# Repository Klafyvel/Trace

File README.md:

Trace
=====

Trace est un projet ayant pour but de créer une traçeuse à commande numérique. Le projet comprend :
- Un utilitaire python pour formater le GCode et le stramer via une liason série à la machine
- Le code (arduino) de la machine qui interprète le GCode et contrôle la machine
- Le plan de la machine (électronique + mécanique)

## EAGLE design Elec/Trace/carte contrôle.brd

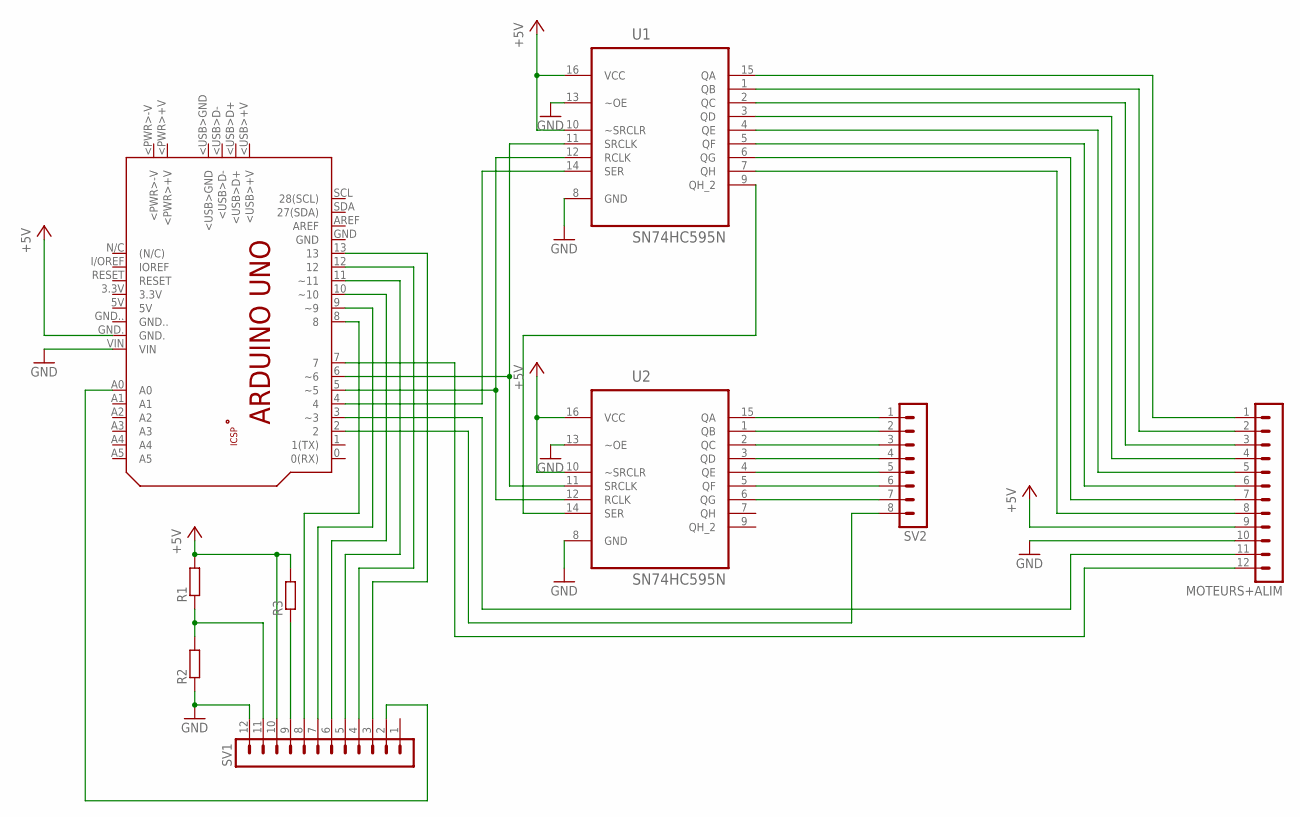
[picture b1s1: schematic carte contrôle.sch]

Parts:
MOTEURS+ALIM: MA12-1
PCB1: ARDUINO_UNO
R1, R2, R3: R-EU_0207/10; 0207/10
SV1: MA12-1
SV2: MA08-1
U1, U2: SN74HC595N; DIP254P762X508-16

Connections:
+5V: MOTEURS+ALIM.9, PCB1.GND., R1.2, R3.2, SV1.10, U1.10 (~SRCLR), U1.16 (VCC), U2.10 (~SRCLR), U2.16 (VCC)
GND: MOTEURS+ALIM.10, PCB1.VIN, R2.1, SV1.12, U1.8 (GND), U1.13 (~OE), U2.8 (GND), U2.13 (~OE)
unnamed: U1.9 (QH_2), U2.14 (SER)
unnamed: MOTEURS+ALIM.1, U1.15 (QA)
unnamed: MOTEURS+ALIM.2, U1.1 (QB)
unnamed: MOTEURS+ALIM.3, U1.2 (QC)
unnamed: MOTEURS+ALIM.4, U1.3 (QD)
unnamed: MOTEURS+ALIM.5, U1.4 (QE)
unnamed: MOTEURS+ALIM.6, U1.5 (QF)
unnamed: MOTEURS+ALIM.7, U1.6 (QG)
unnamed: MOTEURS+ALIM.8, U1.7 (QH)
unnamed: PCB1.5 (~5), U1.12 (RCLK), U2.12 (RCLK)
unnamed: PCB1.6 (~6), U1.11 (SRCLK), U2.11 (SRCLK)
unnamed: PCB1.4, U1.14 (SER)
unnamed: SV2.1, U2.15 (QA)
unnamed: SV2.2, U2.1 (QB)
unnamed: SV2.3, U2.2 (QC)
unnamed: SV2.4, U2.3 (QD)
unnamed: SV2.5, U2.4 (QE)
unnamed: SV2.6, U2.5 (QF)
unnamed: SV2.7, U2.6 (QG)
unnamed: MOTEURS+ALIM.11, PCB1.3 (~3)
unnamed: PCB1.2, SV2.8
unnamed: PCB1.8, SV1.8
unnamed: R1.1, R2.2, SV1.11
unnamed: PCB1.9 (~9), SV1.7
unnamed: PCB1.10 (~10), SV1.6
unnamed: PCB1.11 (~11), SV1.5
unnamed: PCB1.12, SV1.4
unnamed: PCB1.13, SV1.3
unnamed: R3.1, SV1.9
unnamed: PCB1.A0, SV1.2
unnamed: MOTEURS+ALIM.12, PCB1.7

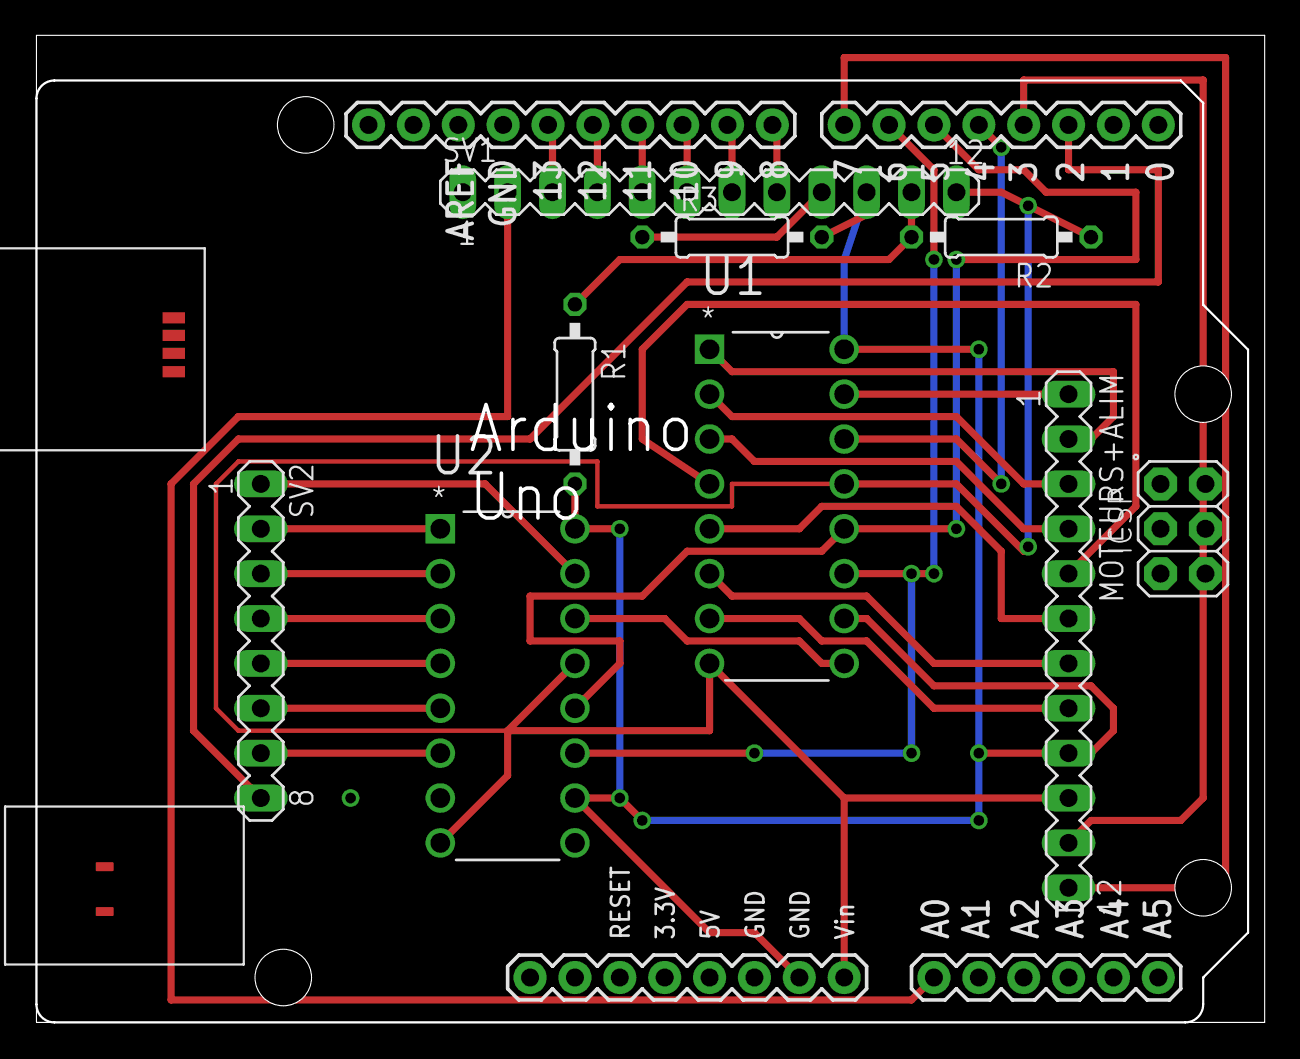
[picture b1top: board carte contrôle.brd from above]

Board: 2 copper layers, 69.5 x 55.8 mm, 9 parts (0 on the bottom side), 33 nets.

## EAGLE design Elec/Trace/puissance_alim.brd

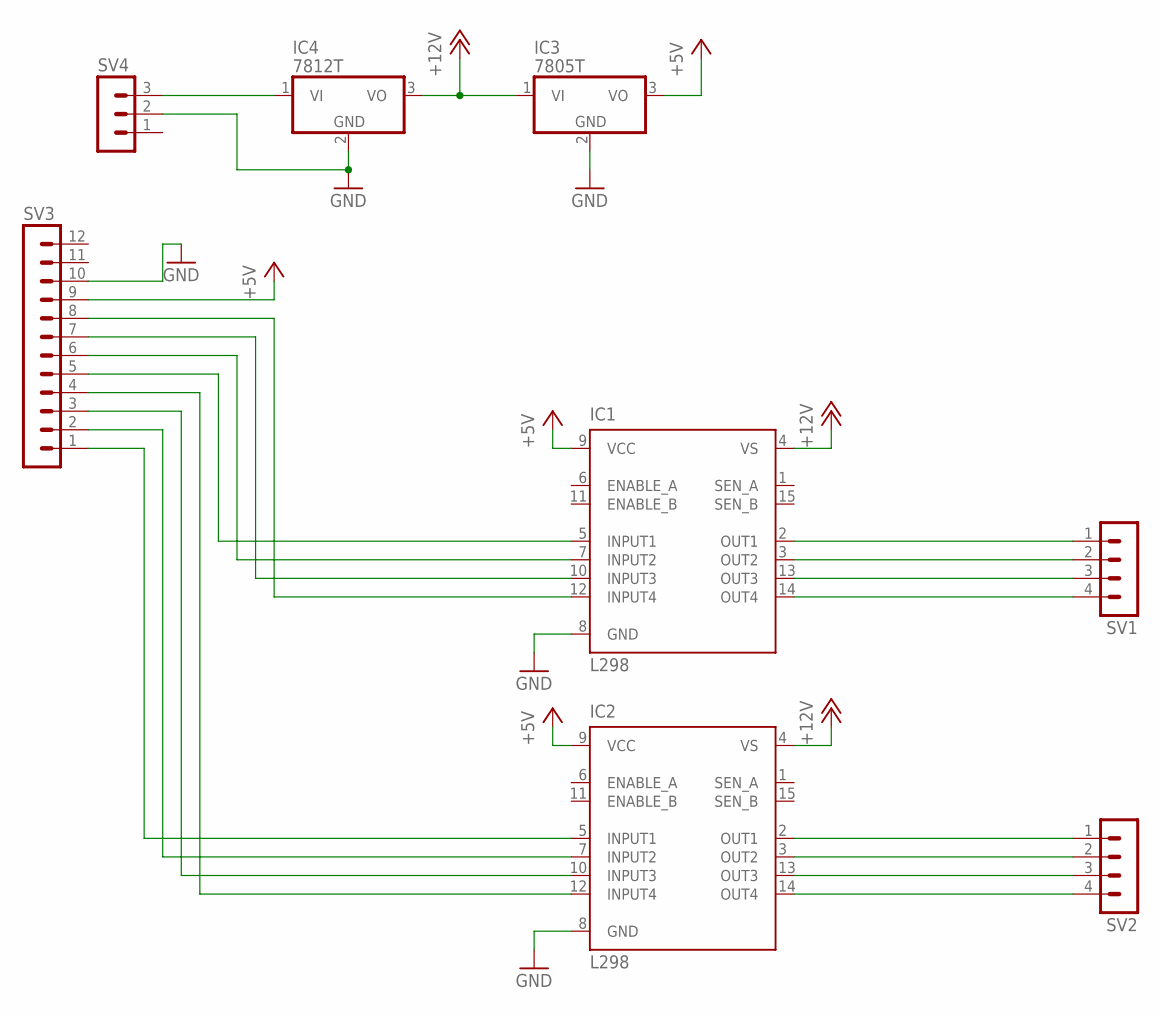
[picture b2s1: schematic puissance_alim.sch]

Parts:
IC1, IC2: L298; MULTIWATT-15
IC3: 7805T; TO220H
IC4: 7812T; TO220H
SV1, SV2: MA04-1
SV3: MA12-1
SV4: MA03-1

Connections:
+5V: IC1.9 (VCC), IC2.9 (VCC), IC3.3 (VO), SV3.9
+12V: IC1.4 (VS), IC2.4 (VS), IC3.1 (VI), IC4.3 (VO)
GND: IC1.8 (GND), IC2.8 (GND), IC3.2 (GND), IC4.2 (GND), SV3.10, SV4.2
unnamed: IC2.5 (INPUT1), SV3.1
unnamed: IC2.7 (INPUT2), SV3.2
unnamed: IC2.10 (INPUT3), SV3.3
unnamed: IC2.12 (INPUT4), SV3.4
unnamed: IC1.5 (INPUT1), SV3.5
unnamed: IC1.7 (INPUT2), SV3.6
unnamed: IC1.10 (INPUT3), SV3.7
unnamed: IC1.12 (INPUT4), SV3.8
unnamed: IC1.2 (OUT1), SV1.1
unnamed: IC1.3 (OUT2), SV1.2
unnamed: IC1.13 (OUT3), SV1.3
unnamed: IC1.14 (OUT4), SV1.4
unnamed: IC2.2 (OUT1), SV2.1
unnamed: IC2.3 (OUT2), SV2.2
unnamed: IC2.13 (OUT3), SV2.3
unnamed: IC2.14 (OUT4), SV2.4
unnamed: IC4.1 (VI), SV4.3

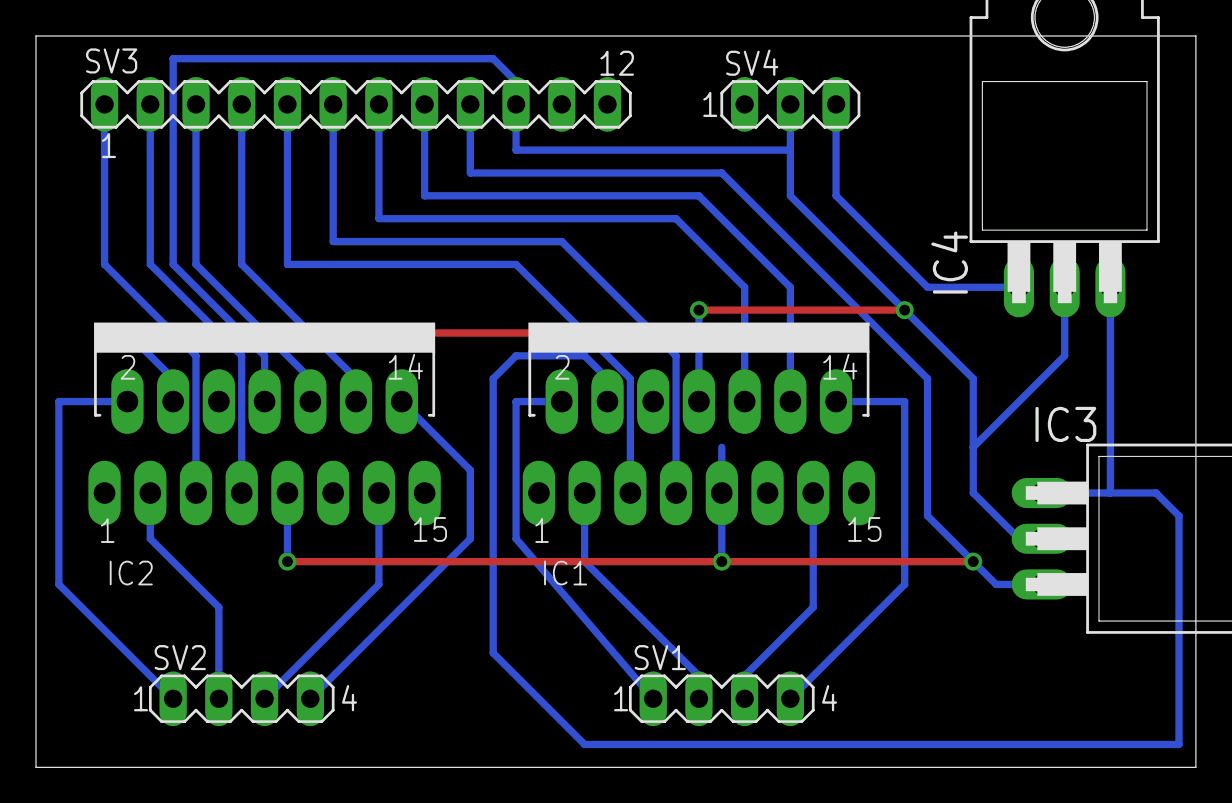
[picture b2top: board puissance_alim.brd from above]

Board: 2 copper layers, 64.4 x 40.6 mm, 8 parts (0 on the bottom side), 20 nets.

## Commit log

2015-05-10 Ajout des fichiers
2015-06-30 GCode parsing
2015-07-01 Header for machine control
2015-07-01 POO + output for steppers
2015-07-01 Began machine implementation.
2015-07-03 Interface pour PC
2015-07-03 Modification de l'interface
2015-07-04 Modification mineure de l'interface
2015-07-04 Liste des ports série disponibles.
2015-07-04 Gestion du port série
2015-07-04 Ajout d'une icone à l'application
2015-07-04 Interface série pour l'utilisateur.
2015-07-04 Ajout d'une option pour les logs.
2015-07-04 Selection du fichier
2015-07-11 Communication machine -> interface utilisateur :D
2015-07-16 Moteur unipolaire
2015-07-16 Commentaire explicatif pour les unités
2015-07-16 Moteurs bipolaires et unipolaires gérés par la même classe.
2015-07-17 Ajout de la lib pour le contrôle des 74HC595
2015-07-17 Ajout d'une macro pour communiquer une valeur binaire.
2015-07-17 Ajout du début du plan de la machine.
2015-07-17 Ajout des schémas électriques.
2015-08-06 Prévisualisation du gcode.
2015-08-06 Fichiers python
2015-08-06 Mise à jour du module ShiftRegister.
2015-08-06 Valeurs définie en cas de non spécification d'argument dans une commande.
2015-08-06 Ajout du nom du site dans le schéma.
2015-08-06 Rapport de performance du module ShiftRegister par vinvin-win
2015-08-07 Édition textuelle du gcode.
2015-08-07 Ajout d'un mode manuel
2015-08-07 fichier log + correction bug mineur sur le mode manuel + adaptation de l'envoi de fichier.
2015-08-07 Interface des contrôles manuels.
2015-08-07 Icônes pour l'interface et action sur la pluspart des commandes.
2015-08-08 meilleure gestion des commentaires
2015-08-08 Ajout du préprocesseur.
2015-08-08 Fichier svg des icônes.
2015-08-08 Ajout de la license.
2015-08-08 Fichiers de l'application.
2015-08-14 Informations sur le projet.
2015-08-17 Envoi de fichier fonctionnel
2015-08-17 Modification d'interface : timeout par défaut à 10 et ports série listés automatiquement
2015-08-17 Correction d'un bug du bouton X- et gestion de l'imprécision du calcul sur les petits arcs
2015-08-17 Gestion des variables dans le G-code
2015-10-22 Fonction de dessin plus courte.
2015-10-22 Ajout de l'option 'effectuer les calculs'.
2015-10-22 Inversion de l'axe y dans la vue de fichier.
2015-10-22 PEP 8
2015-10-22 Supression du rapport.
2015-10-23 Remise à 0 du texte de la fenêtre du préprocesseur.
2015-10-23 Suppression de la segfault à la fermeture du programme.
2015-10-23 Ajout de la lib Listuino.
2015-10-23 Beaucoup de code non commité...
2015-10-28 Ajout d'une simulation basique de port série et d'un fichier gcode exemple.
2022-02-21 [ImgBot] Optimize images
    *Total -- 57.97kb -> 41.99kb (27.56%)
    /PCInterface/traceIcon.svg -- 2.74kb -> 1.05kb (61.66%)
    /PCInterface/icons.svg -- 23.45kb -> 15.20kb (35.16%)
    /PCInterface/reload.png -- 3.98kb -> 2.95kb (25.81%)
    /PCInterface/save.png -- 1.56kb -> 1.18kb (24.15%)
    /PCInterface/work.png -- 12.37kb -> 9.42kb (23.87%)
